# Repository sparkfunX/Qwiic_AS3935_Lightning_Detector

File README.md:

SparkX Qwiic AS3935 Lightning Detector
========================================

[*SparkX Qwiic AS3935 Lightning Detector (SPX-15057)*](https://www.sparkfun.com/products/15057)

Repository Contents
-------------------

* **/Buzzard Labels** - Silkscreen labels for Qwiic AS3935
* **/Documentation** - Data sheets, additional product information
* **/Hardware** - Eagle design files (.brd, .sch)

Documentation
--------------
* **[Installing an Arduino Library](https://learn.sparkfun.com/tutorials/installing-an-arduino-library/)** - Basic instructions on installing an Arduino library
* **[Library](https://github.com/sparkfun/SparkFun_AS3935_Lightning_Detector_Library)** - Arduino library for the Qwiic AS3935 Lightning Detector

License Information
-------------------

This product is _**open source**_! 

Please review the LICENSE.md file for license information.

If you have any questions or concerns on licensing, please contact techsupport@sparkfun.com.

Please use, reuse, and modify these files as you see fit. Please maintain attribution to SparkFun Electronics and release under the same license.

Distributed as-is; no warranty is given.

- Your friends at SparkFun.

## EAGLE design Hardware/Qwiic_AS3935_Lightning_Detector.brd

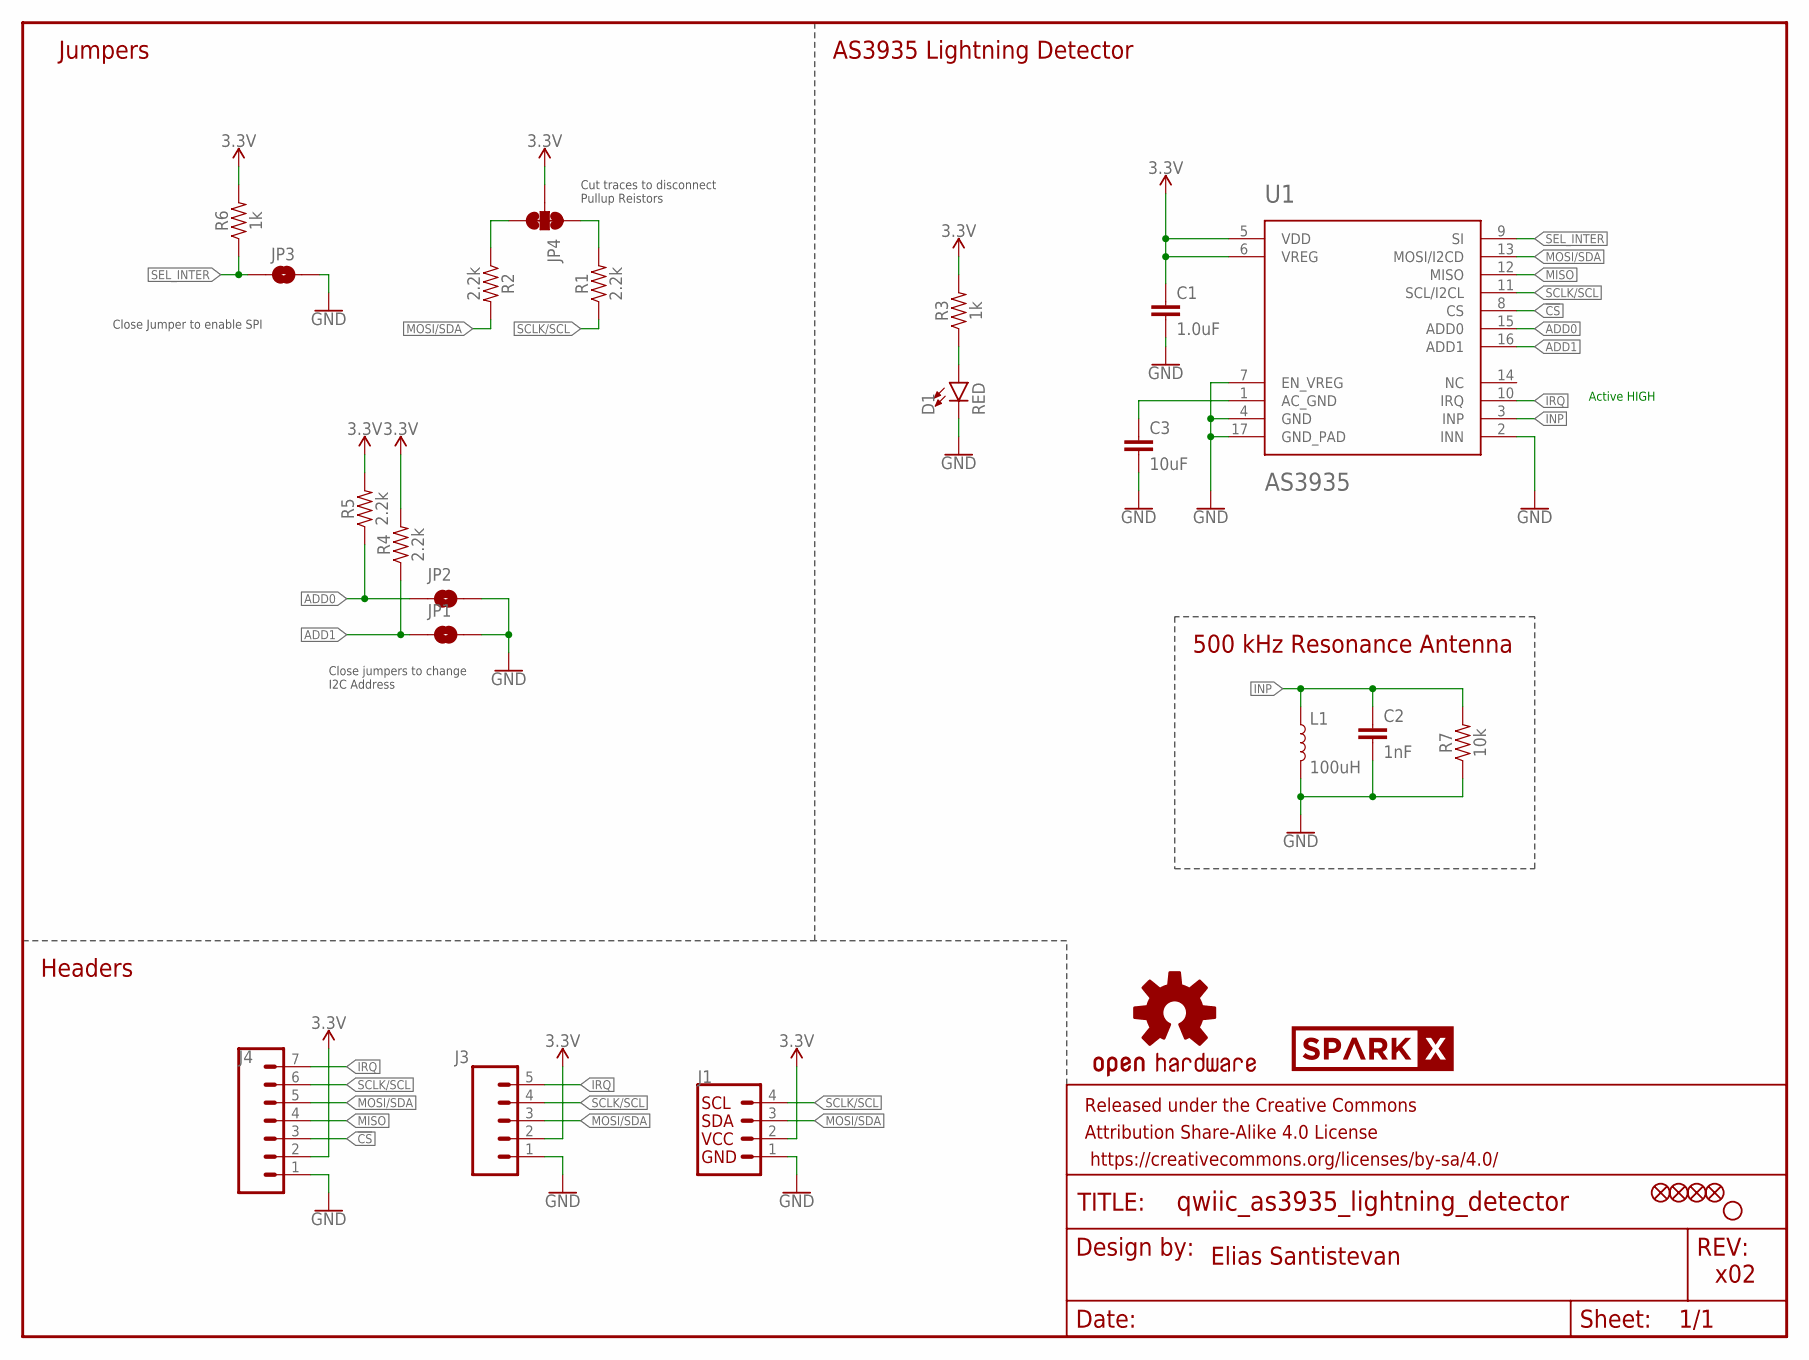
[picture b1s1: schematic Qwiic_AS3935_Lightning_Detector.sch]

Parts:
C1: 1.0uF; 0603
C2: 1nF; 0603
C3: 10uF; 0603
D1: RED; LED-0603
FD1, FD2, FD3, FD4: FIDUCIAL1X2; FIDUCIAL-1X2
FRAME1: FRAME-LETTER; CREATIVE_COMMONS
H1: STAND-OFFTIGHT; STAND-OFF-TIGHT
J1: QWIIC_CONNECTORJS-1MM; 1X04_1MM_RA
J3: CONN_05NO_SILK; 1X05_NO_SILK
J4: CONN_07NO_SILK; 1X07_NO_SILK
JP1, JP2, JP3: JUMPER-SMT_2_NO_SILK; SMT-JUMPER_2_NO_SILK
JP4: JUMPER-SMT_3_2-NC_TRACE_SILK; SMT-JUMPER_3_2-NC_TRACE_SILK
L1: 100uH; MA5532-AE
LOGO1: OSHW-LOGOS; OSHW-LOGO-S
R1, R2, R4, R5: 2.2k; 0603
R3, R6: 1k; 0603
R7: 10k; 0603
U1: AS3935; 16LD_MLPQ
U$1: SPARKX-LOGO2; SPARKX-TINY

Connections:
3.3V: C1.1, J1.2, J3.2, J4.2, JP4.2, R3.2, R4.2, R5.2, R6.2, U1.5 (VDD), U1.6 (VREG)
!CS: J4.3, U1.8 (CS)
ADD0: JP2.1, R5.1, U1.15 (ADD0)
ADD1: JP1.1, R4.1, U1.16 (ADD1)
GND: C1.2, C2.2, C3.2, D1.C, J1.1, J3.1, J4.1, JP1.2, JP2.2, JP3.2, L1.2, R7.1, U1.2 (INN), U1.4 (GND), U1.7 (EN_VREG), U1.17 (GND_PAD)
INP: C2.1, L1.1, R7.2, U1.3 (INP)
IRQ: J3.5, J4.7, U1.10 (IRQ)
MISO: J4.4, U1.12 (MISO)
MOSI/SDA: J1.3, J3.3, J4.5, R2.2, U1.13 (MOSI/I2CD)
unnamed: D1.A, R3.1
unnamed: C3.1, U1.1 (AC_GND)
unnamed: JP4.1, R1.2
unnamed: JP4.3, R2.1
SCLK/SCL: J1.4, J3.4, J4.6, R1.1, U1.11 (SCL/I2CL)
SEL_INTER: JP3.1, R6.1, U1.9 (SI)

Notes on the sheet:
Elias Santistevan
x02
Active HIGH
AS3935 Lightning Detector
Jumpers
Headers
500 kHz Resonance Antenna
Close Jumper to enable SPI
Cut traces to disconnect Pullup Reistors
Close jumpers to change I2C Address

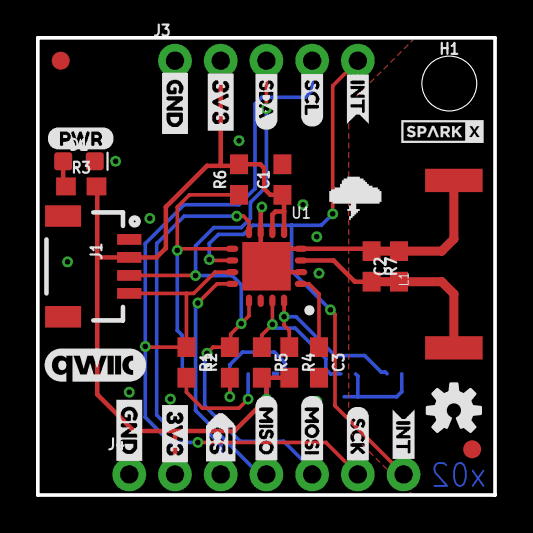
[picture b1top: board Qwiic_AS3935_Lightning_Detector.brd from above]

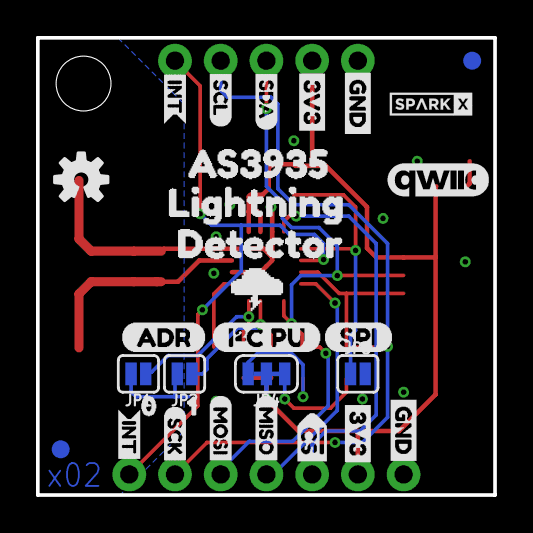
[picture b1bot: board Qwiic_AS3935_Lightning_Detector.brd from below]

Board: 2 copper layers, 25.4 x 25.4 mm, 67 parts (30 on the bottom side), 15 nets.

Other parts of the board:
U$2: SPARKX-TINY
U$3, U$4: QWIIC_COPYRIGHT_SMALL
U$5, U$40: ##0
U$6: AS39350
U$7: LIGHTNING0
U$8, U$9, U$10, U$38: GND-03
U$11: CS#-<]-04
U$12, U$13: MISO-(]-03
U$14, U$15, U$24, U$29: INT0
U$16, U$22: MOSI-(]-03
U$17, U$18, U$20, U$21: 3V3-03
U$19, U$23: SCK-(]-03
U$25, U$26: SDA0
U$27, U$28: SCL0
U$30: #CS0
U$31: OSHW-LOGO-S
U$32: PWR-()-03
U$33: ADR-()-04
U$34: I#C_PU0
U$35: SPI0
U$36: 10
U$37: 00
U$39: DETECTOR0

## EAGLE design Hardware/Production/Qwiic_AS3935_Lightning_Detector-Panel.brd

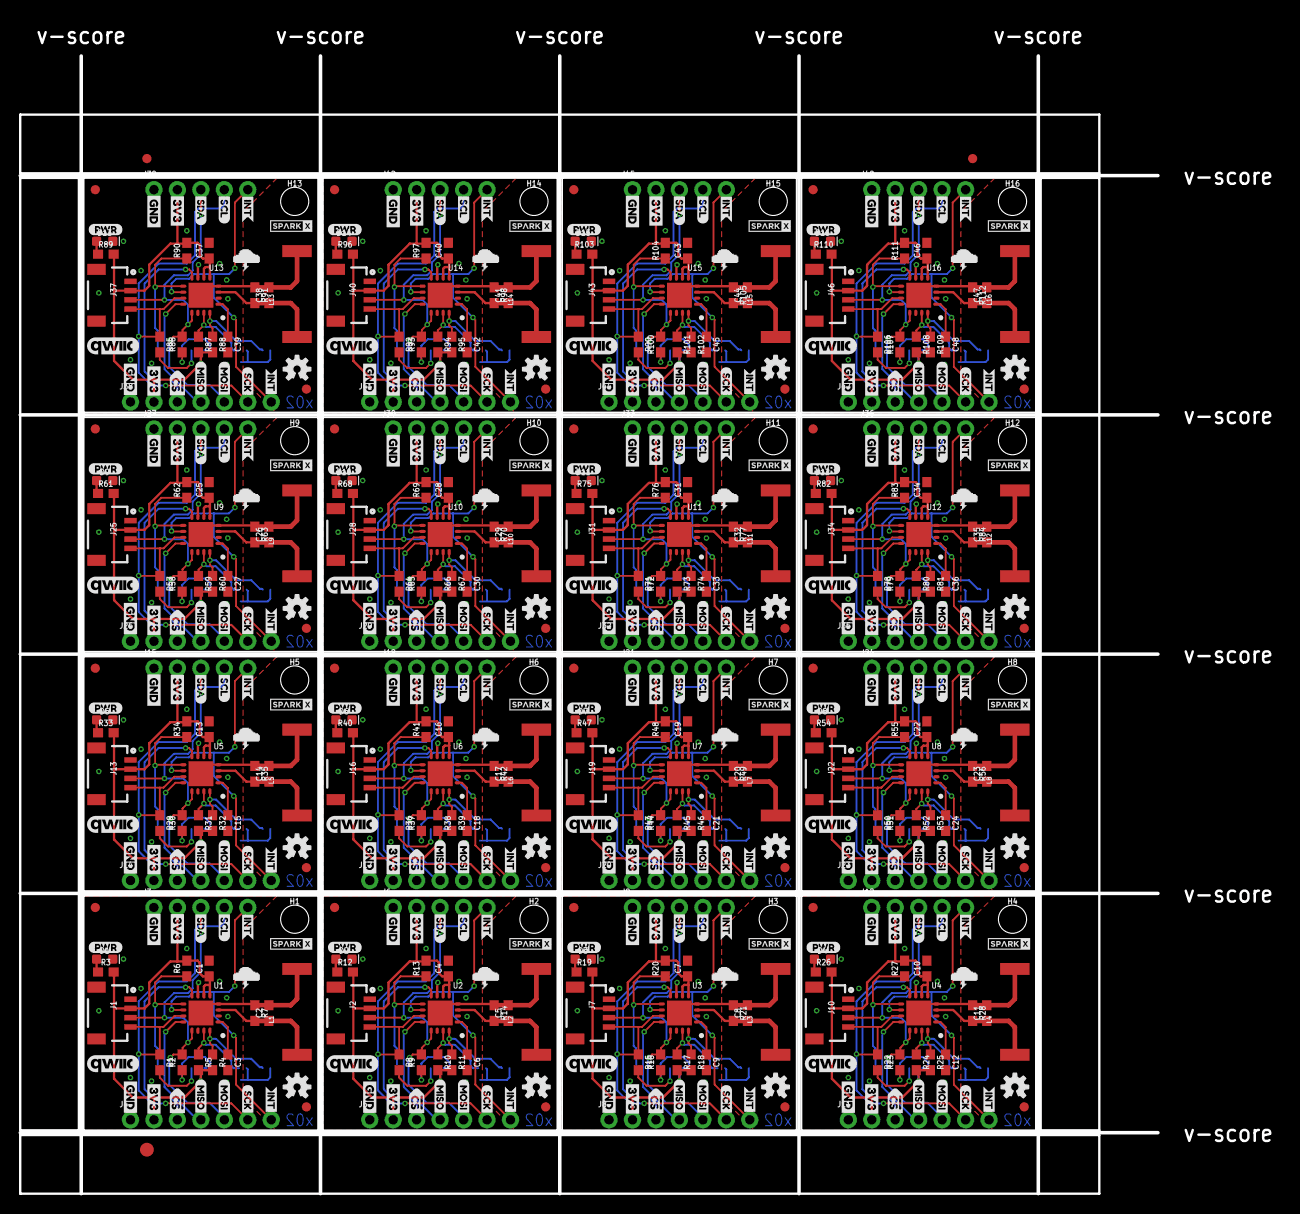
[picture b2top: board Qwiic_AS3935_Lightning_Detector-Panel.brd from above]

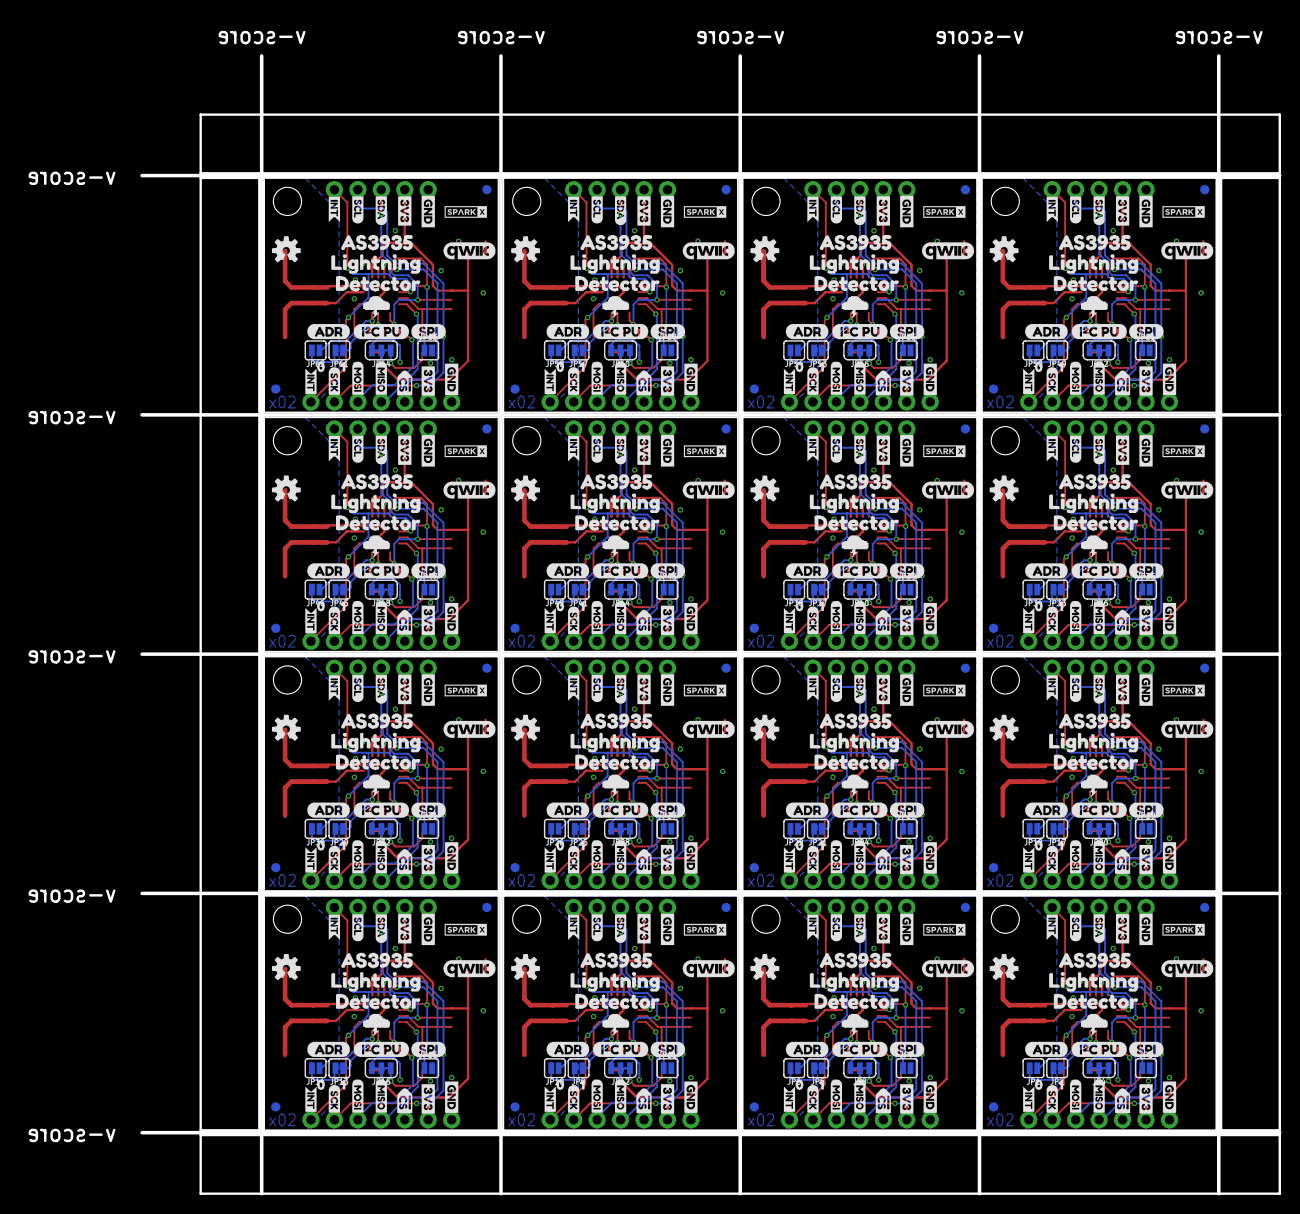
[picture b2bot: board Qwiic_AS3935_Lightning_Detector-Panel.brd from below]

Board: 2 copper layers, 136.4 x 127.1 mm, 1059 parts (480 on the bottom side), 240 nets.

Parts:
C1, C4, C7, C10, C13, C16, C19, C22, C25, C28, C31, C34, C37, C40, C43, C46: 1.0uF; 0603
C2, C5, C8, C11, C14, C17, C20, C23, C26, C29, C32, C35, C38, C41, C44, C47: 1nF; 0603
C3, C6, C9, C12, C15, C18, C21, C24, C27, C30, C33, C36, C39, C42, C45, C48: 10uF; 0603
D1, D2, D3, D4, D5, D6, D7, D8, D9, D10, D11, D12, D13, D14, D15, D16: RED; LED-0603
E$1, E$2: FIDUCIAL-1X2
E$3: FIDUCIAL-1.5X3
FD1, FD2, FD3, FD4, FD5, FD6, FD7, FD8, FD9, FD10, FD11, FD12, FD13, FD14, FD15, FD16, FD17, FD18, FD19, FD20, FD21, FD22, FD23, FD24, FD25, FD26, FD27, FD28, FD29, FD30, FD31, FD32, FD33, FD34, FD35, FD36, FD37, FD38, FD39, FD40, FD41, FD42, FD43, FD44, FD45, FD46, FD47, FD48, FD49, FD50, FD51, FD52, FD53, FD54, FD55, FD56, FD57, FD58, FD59, FD60, FD61, FD62, FD63, FD64: FIDUCIAL1X2; FIDUCIAL-1X2
H1, H2, H3, H4, H5, H6, H7, H8, H9, H10, H11, H12, H13, H14, H15, H16: STAND-OFFTIGHT; STAND-OFF-TIGHT
J1, J2, J7, J10, J13, J16, J19, J22, J25, J28, J31, J34, J37, J40, J43, J46: 1X04_1MM_RA
J3, J6, J9, J12, J15, J18, J21, J24, J27, J30, J33, J36, J39, J42, J45, J48: 1X05_NO_SILK
J4, J5, J8, J11, J14, J17, J20, J23, J26, J29, J32, J35, J38, J41, J44, J47: 1X07_NO_SILK
JP1, JP2, JP3, JP5, JP6, JP7, JP9, JP10, JP11, JP13, JP14, JP15, JP17, JP18, JP19, JP21, JP22, JP23, JP25, JP26, JP27, JP29, JP30, JP31, JP33, JP34, JP35, JP37, JP38, JP39, JP41, JP42, JP43, JP45, JP46, JP47, JP49, JP50, JP51, JP53, JP54, JP55, JP57, JP58, JP59, JP61, JP62, JP63: JUMPER-SMT_2_NO_SILK; SMT-JUMPER_2_NO_SILK
JP4, JP8, JP12, JP16, JP20, JP24, JP28, JP32, JP36, JP40, JP44, JP48, JP52, JP56, JP60, JP64: JUMPER-SMT_3_2-NC_TRACE_SILK; SMT-JUMPER_3_2-NC_TRACE_SILK
L1, L2, L3, L4, L5, L6, L7, L8, L9, L10, L11, L12, L13, L14, L15, L16: 100uH; MA5532-AE
LOGO1, LOGO2, LOGO3, LOGO4, LOGO5, LOGO6, LOGO7, LOGO8, LOGO9, LOGO10, LOGO11, LOGO12, LOGO13, LOGO14, LOGO15, LOGO16: OSHW-LOGOS; OSHW-LOGO-S
R1, R2, R4, R5, R8, R9, R10, R11, R15, R16, R17, R18, R22, R23, R24, R25, R29, R30, R31, R32, R36, R37, R38, R39, R43, R44, R45, R46, R50, R51, R52, R53, R57, R58, R59, R60, R64, R65, R66, R67, R71, R72, R73, R74, R78, R79, R80, R81, R85, R86, R87, R88, R92, R93, R94, R95, R99, R100, R101, R102, R106, R107, R108, R109: 2.2k; 0603
R3, R6, R12, R13, R19, R20, R26, R27, R33, R34, R40, R41, R47, R48, R54, R55, R61, R62, R68, R69, R75, R76, R82, R83, R89, R90, R96, R97, R103, R104, R110, R111: 1k; 0603
R7, R14, R21, R28, R35, R42, R49, R56, R63, R70, R77, R84, R91, R98, R105, R112: 10k; 0603
U1, U2, U3, U4, U5, U6, U7, U8, U9, U10, U11, U12, U13, U14, U15, U16: AS3935; 16LD_MLPQ
U$1, U$41, U$81, U$121, U$161, U$201, U$241, U$281, U$321, U$361, U$401, U$441, U$481, U$521, U$561, U$601: SPARKX-LOGO2; SPARKX-TINY
U$2, U$42, U$82, U$122, U$162, U$202, U$242, U$282, U$322, U$362, U$402, U$442, U$482, U$522, U$562, U$602: SPARKX-TINY
U$3, U$4, U$43, U$44, U$83, U$84, U$123, U$124, U$163, U$164, U$203, U$204, U$243, U$244, U$283, U$284, U$323, U$324, U$363, U$364, U$403, U$404, U$443, U$444, U$483, U$484, U$523, U$524, U$563, U$564, U$603, U$604: QWIIC_COPYRIGHT_SMALL
U$5, U$40, U$67, U$68, U$107, U$108, U$147, U$148, U$187, U$188, U$227, U$228, U$267, U$268, U$307, U$308, U$347, U$348, U$387, U$388, U$427, U$428, U$467, U$468, U$507, U$508, U$547, U$548, U$587, U$588, U$627, U$628: ##0
U$6, U$64, U$104, U$144, U$184, U$224, U$264, U$304, U$344, U$384, U$424, U$464, U$504, U$544, U$584, U$624: AS39350
U$7, U$65, U$105, U$145, U$185, U$225, U$265, U$305, U$345, U$385, U$425, U$465, U$505, U$545, U$585, U$625: LIGHTNING0
U$8, U$9, U$10, U$38, U$45, U$46, U$63, U$69, U$85, U$86, U$103, U$109, U$125, U$126, U$143, U$149, U$165, U$166, U$183, U$189, U$205, U$206, U$223, U$229, U$245, U$246, U$263, U$269, U$285, U$286, U$303, U$309, U$325, U$326, U$343, U$349, U$365, U$366, U$383, U$389, U$405, U$406, U$423, U$429, U$445, U$446, U$463, U$469, U$485, U$486, U$503, U$509, U$525, U$526, U$543, U$549, U$565, U$566, U$583, U$589, U$605, U$606, U$623, U$629: GND-03
U$11, U$70, U$110, U$150, U$190, U$230, U$270, U$310, U$350, U$390, U$430, U$470, U$510, U$550, U$590, U$630: CS#-<]-04
U$12, U$13, U$47, U$72, U$87, U$112, U$127, U$152, U$167, U$192, U$207, U$232, U$247, U$272, U$287, U$312, U$327, U$352, U$367, U$392, U$407, U$432, U$447, U$472, U$487, U$512, U$527, U$552, U$567, U$592, U$607, U$632: MISO-(]-03
U$14, U$15, U$24, U$29, U$74, U$75, U$76, U$77, U$114, U$115, U$116, U$117, U$154, U$155, U$156, U$157, U$194, U$195, U$196, U$197, U$234, U$235, U$236, U$237, U$274, U$275, U$276, U$277, U$314, U$315, U$316, U$317, U$354, U$355, U$356, U$357, U$394, U$395, U$396, U$397, U$434, U$435, U$436, U$437, U$474, U$475, U$476, U$477, U$514, U$515, U$516, U$517, U$554, U$555, U$556, U$557, U$594, U$595, U$596, U$597, U$634, U$635, U$636, U$637: INT0
U$16, U$22, U$71, U$78, U$111, U$118, U$151, U$158, U$191, U$198, U$231, U$238, U$271, U$278, U$311, U$318, U$351, U$358, U$391, U$398, U$431, U$438, U$471, U$478, U$511, U$518, U$551, U$558, U$591, U$598, U$631, U$638: MOSI-(]-03
U$17, U$18, U$20, U$21, U$48, U$49, U$50, U$51, U$88, U$89, U$90, U$91, U$128, U$129, U$130, U$131, U$168, U$169, U$170, U$171, U$208, U$209, U$210, U$211, U$248, U$249, U$250, U$251, U$288, U$289, U$290, U$291, U$328, U$329, U$330, U$331, U$368, U$369, U$370, U$371, U$408, U$409, U$410, U$411, U$448, U$449, U$450, U$451, U$488, U$489, U$490, U$491, U$528, U$529, U$530, U$531, U$568, U$569, U$570, U$571, U$608, U$609, U$610, U$611: 3V3-03
U$19, U$23, U$73, U$79, U$113, U$119, U$153, U$159, U$193, U$199, U$233, U$239, U$273, U$279, U$313, U$319, U$353, U$359, U$393, U$399, U$433, U$439, U$473, U$479, U$513, U$519, U$553, U$559, U$593, U$599, U$633, U$639: SCK-(]-03
U$25, U$26, U$52, U$53, U$92, U$93, U$132, U$133, U$172, U$173, U$212, U$213, U$252, U$253, U$292, U$293, U$332, U$333, U$372, U$373, U$412, U$413, U$452, U$453, U$492, U$493, U$532, U$533, U$572, U$573, U$612, U$613: SDA0
U$27, U$28, U$54, U$55, U$94, U$95, U$134, U$135, U$174, U$175, U$214, U$215, U$254, U$255, U$294, U$295, U$334, U$335, U$374, U$375, U$414, U$415, U$454, U$455, U$494, U$495, U$534, U$535, U$574, U$575, U$614, U$615: SCL0
U$30, U$80, U$120, U$160, U$200, U$240, U$280, U$320, U$360, U$400, U$440, U$480, U$520, U$560, U$600, U$640: #CS0
U$31, U$56, U$96, U$136, U$176, U$216, U$256, U$296, U$336, U$376, U$416, U$456, U$496, U$536, U$576, U$616: OSHW-LOGO-S
U$32, U$57, U$97, U$137, U$177, U$217, U$257, U$297, U$337, U$377, U$417, U$457, U$497, U$537, U$577, U$617: PWR-()-03
U$33, U$58, U$98, U$138, U$178, U$218, U$258, U$298, U$338, U$378, U$418, U$458, U$498, U$538, U$578, U$618: ADR-()-04
U$34, U$59, U$99, U$139, U$179, U$219, U$259, U$299, U$339, U$379, U$419, U$459, U$499, U$539, U$579, U$619: I#C_PU0
U$35, U$60, U$100, U$140, U$180, U$220, U$260, U$300, U$340, U$380, U$420, U$460, U$500, U$540, U$580, U$620: SPI0
U$36, U$61, U$101, U$141, U$181, U$221, U$261, U$301, U$341, U$381, U$421, U$461, U$501, U$541, U$581, U$621: 10
U$37, U$62, U$102, U$142, U$182, U$222, U$262, U$302, U$342, U$382, U$422, U$462, U$502, U$542, U$582, U$622: 00
U$39, U$66, U$106, U$146, U$186, U$226, U$266, U$306, U$346, U$386, U$426, U$466, U$506, U$546, U$586, U$626: DETECTOR0

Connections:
3.3V: C1.1, J1.2, J3.2, J4.2, JP4.2, R3.2, R4.2, R5.2, R6.2, U1.5, U1.6
3.3V1: C4.1, J2.2, J5.2, J6.2, JP8.2, R10.2, R11.2, R12.2, R13.2, U2.5, U2.6
3.3V2: C7.1, J7.2, J8.2, J9.2, JP12.2, R17.2, R18.2, R19.2, R20.2, U3.5, U3.6
3.3V3: C10.1, J10.2, J11.2, J12.2, JP16.2, R24.2, R25.2, R26.2, R27.2, U4.5, U4.6
3.3V4: C13.1, J13.2, J14.2, J15.2, JP20.2, R31.2, R32.2, R33.2, R34.2, U5.5, U5.6
3.3V5: C16.1, J16.2, J17.2, J18.2, JP24.2, R38.2, R39.2, R40.2, R41.2, U6.5, U6.6
3.3V6: C19.1, J19.2, J20.2, J21.2, JP28.2, R45.2, R46.2, R47.2, R48.2, U7.5, U7.6
3.3V7: C22.1, J22.2, J23.2, J24.2, JP32.2, R52.2, R53.2, R54.2, R55.2, U8.5, U8.6
3.3V8: C25.1, J25.2, J26.2, J27.2, JP36.2, R59.2, R60.2, R61.2, R62.2, U9.5, U9.6
3.3V9: C28.1, J28.2, J29.2, J30.2, JP40.2, R66.2, R67.2, R68.2, R69.2, U10.5, U10.6
3.3V10: C31.1, J31.2, J32.2, J33.2, JP44.2, R73.2, R74.2, R75.2, R76.2, U11.5, U11.6
3.3V11: C34.1, J34.2, J35.2, J36.2, JP48.2, R80.2, R81.2, R82.2, R83.2, U12.5, U12.6
3.3V12: C37.1, J37.2, J38.2, J39.2, JP52.2, R87.2, R88.2, R89.2, R90.2, U13.5, U13.6
3.3V13: C40.1, J40.2, J41.2, J42.2, JP56.2, R94.2, R95.2, R96.2, R97.2, U14.5, U14.6
3.3V14: C43.1, J43.2, J44.2, J45.2, JP60.2, R101.2, R102.2, R103.2, R104.2, U15.5, U15.6
3.3V15: C46.1, J46.2, J47.2, J48.2, JP64.2, R108.2, R109.2, R110.2, R111.2, U16.5, U16.6
!CS: J4.3, U1.8
!CS1: J5.3, U2.8
!CS2: J8.3, U3.8
!CS3: J11.3, U4.8
!CS4: J14.3, U5.8
!CS5: J17.3, U6.8
!CS6: J20.3, U7.8
!CS7: J23.3, U8.8
!CS8: J26.3, U9.8
!CS9: J29.3, U10.8
!CS10: J32.3, U11.8
!CS11: J35.3, U12.8
!CS12: J38.3, U13.8
!CS13: J41.3, U14.8
!CS14: J44.3, U15.8
!CS15: J47.3, U16.8
ADD0: JP2.1, R5.1, U1.15
ADD1: JP1.1, R4.1, U1.16
ADD2: JP5.1, R10.1, U2.15
ADD3: JP6.1, R11.1, U2.16
ADD4: JP9.1, R17.1, U3.15
ADD5: JP10.1, R18.1, U3.16
ADD6: JP13.1, R24.1, U4.15
ADD7: JP14.1, R25.1, U4.16
ADD8: JP17.1, R31.1, U5.15
ADD9: JP18.1, R32.1, U5.16
ADD10: JP21.1, R38.1, U6.15
ADD11: JP22.1, R39.1, U6.16
ADD12: JP25.1, R45.1, U7.15
ADD13: JP26.1, R46.1, U7.16
ADD14: JP29.1, R52.1, U8.15
ADD15: JP30.1, R53.1, U8.16
ADD16: JP33.1, R59.1, U9.15
ADD17: JP34.1, R60.1, U9.16
ADD18: JP37.1, R66.1, U10.15
ADD19: JP38.1, R67.1, U10.16
ADD20: JP41.1, R73.1, U11.15
ADD21: JP42.1, R74.1, U11.16
ADD22: JP45.1, R80.1, U12.15
ADD23: JP46.1, R81.1, U12.16
ADD24: JP49.1, R87.1, U13.15
ADD25: JP50.1, R88.1, U13.16
ADD26: JP53.1, R94.1, U14.15
ADD27: JP54.1, R95.1, U14.16
ADD28: JP57.1, R101.1, U15.15
ADD29: JP58.1, R102.1, U15.16
ADD30: JP61.1, R108.1, U16.15
ADD31: JP62.1, R109.1, U16.16
GND: C1.2, C2.2, C3.2, D1.C, J1.1, J3.1, J4.1, JP1.2, JP2.2, JP3.2, L1.2, R7.1, U1.2, U1.4, U1.7, U1.17
GND1: C4.2, C5.2, C6.2, D2.C, J2.1, J5.1, J6.1, JP5.2, JP6.2, JP7.2, L2.2, R14.1, U2.2, U2.4, U2.7, U2.17
GND2: C7.2, C8.2, C9.2, D3.C, J7.1, J8.1, J9.1, JP9.2, JP10.2, JP11.2, L3.2, R21.1, U3.2, U3.4, U3.7, U3.17
GND3: C10.2, C11.2, C12.2, D4.C, J10.1, J11.1, J12.1, JP13.2, JP14.2, JP15.2, L4.2, R28.1, U4.2, U4.4, U4.7, U4.17
GND4: C13.2, C14.2, C15.2, D5.C, J13.1, J14.1, J15.1, JP17.2, JP18.2, JP19.2, L5.2, R35.1, U5.2, U5.4, U5.7, U5.17
GND5: C16.2, C17.2, C18.2, D6.C, J16.1, J17.1, J18.1, JP21.2, JP22.2, JP23.2, L6.2, R42.1, U6.2, U6.4, U6.7, U6.17
GND6: C19.2, C20.2, C21.2, D7.C, J19.1, J20.1, J21.1, JP25.2, JP26.2, JP27.2, L7.2, R49.1, U7.2, U7.4, U7.7, U7.17
GND7: C22.2, C23.2, C24.2, D8.C, J22.1, J23.1, J24.1, JP29.2, JP30.2, JP31.2, L8.2, R56.1, U8.2, U8.4, U8.7, U8.17
GND8: C25.2, C26.2, C27.2, D9.C, J25.1, J26.1, J27.1, JP33.2, JP34.2, JP35.2, L9.2, R63.1, U9.2, U9.4, U9.7, U9.17
GND9: C28.2, C29.2, C30.2, D10.C, J28.1, J29.1, J30.1, JP37.2, JP38.2, JP39.2, L10.2, R70.1, U10.2, U10.4, U10.7, U10.17
GND10: C31.2, C32.2, C33.2, D11.C, J31.1, J32.1, J33.1, JP41.2, JP42.2, JP43.2, L11.2, R77.1, U11.2, U11.4, U11.7, U11.17
GND11: C34.2, C35.2, C36.2, D12.C, J34.1, J35.1, J36.1, JP45.2, JP46.2, JP47.2, L12.2, R84.1, U12.2, U12.4, U12.7, U12.17
GND12: C37.2, C38.2, C39.2, D13.C, J37.1, J38.1, J39.1, JP49.2, JP50.2, JP51.2, L13.2, R91.1, U13.2, U13.4, U13.7, U13.17
GND13: C40.2, C41.2, C42.2, D14.C, J40.1, J41.1, J42.1, JP53.2, JP54.2, JP55.2, L14.2, R98.1, U14.2, U14.4, U14.7, U14.17
GND14: C43.2, C44.2, C45.2, D15.C, J43.1, J44.1, J45.1, JP57.2, JP58.2, JP59.2, L15.2, R105.1, U15.2, U15.4, U15.7, U15.17
GND15: C46.2, C47.2, C48.2, D16.C, J46.1, J47.1, J48.1, JP61.2, JP62.2, JP63.2, L16.2, R112.1, U16.2, U16.4, U16.7, U16.17
INP: C2.1, L1.1, R7.2, U1.3
INP1: C5.1, L2.1, R14.2, U2.3
INP2: C8.1, L3.1, R21.2, U3.3
INP3: C11.1, L4.1, R28.2, U4.3
INP4: C14.1, L5.1, R35.2, U5.3
INP5: C17.1, L6.1, R42.2, U6.3
INP6: C20.1, L7.1, R49.2, U7.3
INP7: C23.1, L8.1, R56.2, U8.3
INP8: C26.1, L9.1, R63.2, U9.3
INP9: C29.1, L10.1, R70.2, U10.3
INP10: C32.1, L11.1, R77.2, U11.3
INP11: C35.1, L12.1, R84.2, U12.3
INP12: C38.1, L13.1, R91.2, U13.3
INP13: C41.1, L14.1, R98.2, U14.3
INP14: C44.1, L15.1, R105.2, U15.3
INP15: C47.1, L16.1, R112.2, U16.3
IRQ: J3.5, J4.7, U1.10
IRQ1: J5.7, J6.5, U2.10
IRQ2: J8.7, J9.5, U3.10
IRQ3: J11.7, J12.5, U4.10
IRQ4: J14.7, J15.5, U5.10
IRQ5: J17.7, J18.5, U6.10
IRQ6: J20.7, J21.5, U7.10
IRQ7: J23.7, J24.5, U8.10
IRQ8: J26.7, J27.5, U9.10
IRQ9: J29.7, J30.5, U10.10
IRQ10: J32.7, J33.5, U11.10
IRQ11: J35.7, J36.5, U12.10
IRQ12: J38.7, J39.5, U13.10
IRQ13: J41.7, J42.5, U14.10
IRQ14: J44.7, J45.5, U15.10
IRQ15: J47.7, J48.5, U16.10
MISO: J4.4, U1.12
MISO1: J5.4, U2.12
MISO2: J8.4, U3.12
MISO3: J11.4, U4.12
MISO4: J14.4, U5.12
MISO5: J17.4, U6.12
MISO6: J20.4, U7.12
MISO7: J23.4, U8.12
MISO8: J26.4, U9.12
MISO9: J29.4, U10.12
MISO10: J32.4, U11.12
MISO11: J35.4, U12.12
MISO12: J38.4, U13.12
MISO13: J41.4, U14.12
MISO14: J44.4, U15.12
MISO15: J47.4, U16.12
MOSI/SDA: J1.3, J3.3, J4.5, R2.2, U1.13
MOSI/SDA1: J2.3, J5.5, J6.3, R9.2, U2.13
MOSI/SDA2: J7.3, J8.5, J9.3, R16.2, U3.13
MOSI/SDA3: J10.3, J11.5, J12.3, R23.2, U4.13
MOSI/SDA4: J13.3, J14.5, J15.3, R30.2, U5.13
MOSI/SDA5: J16.3, J17.5, J18.3, R37.2, U6.13
MOSI/SDA6: J19.3, J20.5, J21.3, R44.2, U7.13
MOSI/SDA7: J22.3, J23.5, J24.3, R51.2, U8.13
MOSI/SDA8: J25.3, J26.5, J27.3, R58.2, U9.13
MOSI/SDA9: J28.3, J29.5, J30.3, R65.2, U10.13
MOSI/SDA10: J31.3, J32.5, J33.3, R72.2, U11.13
MOSI/SDA11: J34.3, J35.5, J36.3, R79.2, U12.13
MOSI/SDA12: J37.3, J38.5, J39.3, R86.2, U13.13
MOSI/SDA13: J40.3, J41.5, J42.3, R93.2, U14.13
MOSI/SDA14: J43.3, J44.5, J45.3, R100.2, U15.13
MOSI/SDA15: J46.3, J47.5, J48.3, R107.2, U16.13
unnamed: D1.A, R3.1
unnamed: C3.1, U1.1
unnamed: JP4.1, R1.2
unnamed: JP4.3, R2.1
unnamed: D2.A, R12.1
unnamed: C6.1, U2.1
unnamed: JP8.1, R8.2
unnamed: JP8.3, R9.1
unnamed: D3.A, R19.1
unnamed: C9.1, U3.1
unnamed: JP12.1, R15.2
unnamed: JP12.3, R16.1
unnamed: D4.A, R26.1
unnamed: C12.1, U4.1
unnamed: JP16.1, R22.2
unnamed: JP16.3, R23.1
unnamed: D5.A, R33.1
unnamed: C15.1, U5.1
unnamed: JP20.1, R29.2
unnamed: JP20.3, R30.1
unnamed: D6.A, R40.1
unnamed: C18.1, U6.1
unnamed: JP24.1, R36.2
unnamed: JP24.3, R37.1
unnamed: D7.A, R47.1
unnamed: C21.1, U7.1
unnamed: JP28.1, R43.2
unnamed: JP28.3, R44.1
unnamed: D8.A, R54.1
unnamed: C24.1, U8.1
unnamed: JP32.1, R50.2
unnamed: JP32.3, R51.1
unnamed: D9.A, R61.1
unnamed: C27.1, U9.1
unnamed: JP36.1, R57.2
unnamed: JP36.3, R58.1
unnamed: D10.A, R68.1
unnamed: C30.1, U10.1
unnamed: JP40.1, R64.2
unnamed: JP40.3, R65.1
unnamed: D11.A, R75.1
unnamed: C33.1, U11.1
unnamed: JP44.1, R71.2
unnamed: JP44.3, R72.1
unnamed: D12.A, R82.1
unnamed: C36.1, U12.1
unnamed: JP48.1, R78.2
unnamed: JP48.3, R79.1
unnamed: D13.A, R89.1
unnamed: C39.1, U13.1
unnamed: JP52.1, R85.2
unnamed: JP52.3, R86.1
unnamed: D14.A, R96.1
unnamed: C42.1, U14.1
unnamed: JP56.1, R92.2
unnamed: JP56.3, R93.1
unnamed: D15.A, R103.1
unnamed: C45.1, U15.1
unnamed: JP60.1, R99.2
unnamed: JP60.3, R100.1
unnamed: D16.A, R110.1
unnamed: C48.1, U16.1
unnamed: JP64.1, R106.2
unnamed: JP64.3, R107.1
SCLK/SCL: J1.4, J3.4, J4.6, R1.1, U1.11
SCLK/SCL1: J2.4, J5.6, J6.4, R8.1, U2.11
SCLK/SCL2: J7.4, J8.6, J9.4, R15.1, U3.11
SCLK/SCL3: J10.4, J11.6, J12.4, R22.1, U4.11
SCLK/SCL4: J13.4, J14.6, J15.4, R29.1, U5.11
SCLK/SCL5: J16.4, J17.6, J18.4, R36.1, U6.11
SCLK/SCL6: J19.4, J20.6, J21.4, R43.1, U7.11
SCLK/SCL7: J22.4, J23.6, J24.4, R50.1, U8.11
SCLK/SCL8: J25.4, J26.6, J27.4, R57.1, U9.11
SCLK/SCL9: J28.4, J29.6, J30.4, R64.1, U10.11
SCLK/SCL10: J31.4, J32.6, J33.4, R71.1, U11.11
SCLK/SCL11: J34.4, J35.6, J36.4, R78.1, U12.11
SCLK/SCL12: J37.4, J38.6, J39.4, R85.1, U13.11
SCLK/SCL13: J40.4, J41.6, J42.4, R92.1, U14.11
SCLK/SCL14: J43.4, J44.6, J45.4, R99.1, U15.11
SCLK/SCL15: J46.4, J47.6, J48.4, R106.1, U16.11
SEL_INTER: JP3.1, R6.1, U1.9
SEL_INTER1: JP7.1, R13.1, U2.9
SEL_INTER2: JP11.1, R20.1, U3.9
SEL_INTER3: JP15.1, R27.1, U4.9
SEL_INTER4: JP19.1, R34.1, U5.9
SEL_INTER5: JP23.1, R41.1, U6.9
SEL_INTER6: JP27.1, R48.1, U7.9
SEL_INTER7: JP31.1, R55.1, U8.9
SEL_INTER8: JP35.1, R62.1, U9.9
SEL_INTER9: JP39.1, R69.1, U10.9
SEL_INTER10: JP43.1, R76.1, U11.9
SEL_INTER11: JP47.1, R83.1, U12.9
SEL_INTER12: JP51.1, R90.1, U13.9
SEL_INTER13: JP55.1, R97.1, U14.9
SEL_INTER14: JP59.1, R104.1, U15.9
SEL_INTER15: JP63.1, R111.1, U16.9

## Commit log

2018-10-19 Initial Commit x01
2018-10-19 Library update, small changeds to PCB
2018-10-19 Panel created
2018-10-19 Fixed AS3935 SKU in library
2018-10-31 Version x02 Exposed pad underneath was not connected to ground, coil package was incorrect.
2018-10-31 One more time
2019-01-08 Updates README and deletes unnecssary production files.
2019-01-08 Adds Creative Commons License
2019-01-09 Update and rename Readme.md to README.md
    - Link Arduino library and how to install an Arduino library.
    - Adjust list Repository Contents
    - Fix markdown. =)
2019-01-15 Updates link to library in README

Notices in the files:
parts and their libraries:
SparkFun-Aesthetics: Licensing: Creative Commons ShareAlike 4.0 International - https://creativecommons.org/licenses/by-sa/4.0
SparkFun-Aesthetics: Released under the Creative Commons Attribution Share-Alike 4.0 License
SparkFun-Aesthetics: https://creativecommons.org/licenses/by-sa/4.0
